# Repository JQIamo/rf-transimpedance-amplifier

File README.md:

# RF Transimpedance Amplifier

An AC-coupled transimpedance amplifier, for use in (eg) beatnote or PDH locks.

Still a work in progress, more info to come soon.

NOTE: Despite git commit history, the pdh-photodiode branch is more up to date than master for the ac-coupled transimpedance amp (I believe...)

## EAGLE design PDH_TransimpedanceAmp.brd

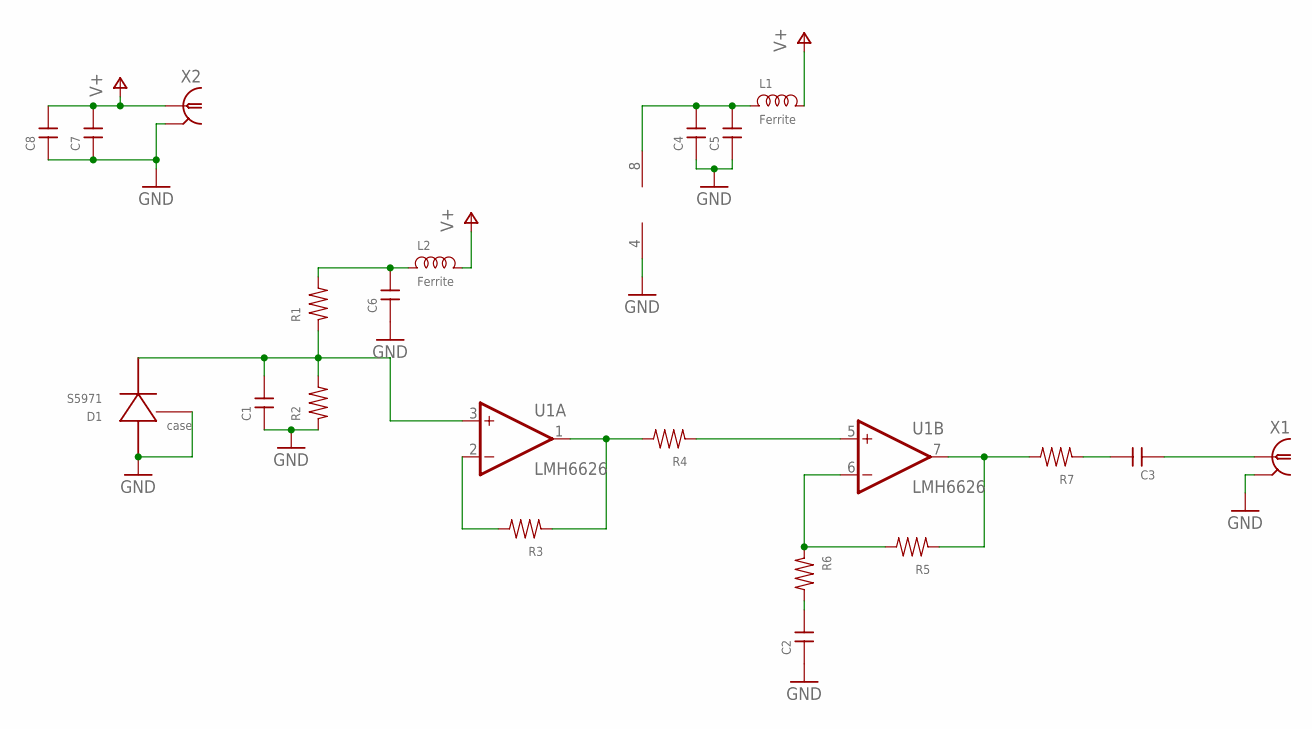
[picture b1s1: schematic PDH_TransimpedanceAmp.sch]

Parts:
C1, C2, C3, C4, C8: CAP0402; 0402
C5, C6, C7: CAP0805; 0805
D1: S5971; S5971-CASE
L1, L2: Ferrite; 0805
R1, R2, R3, R4, R5, R6, R7: RES0402; 0402
U1: LMH6626; SO08
X1, X2: UMC

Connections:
GND: C1.1, C2.1, C4.1, C5.1, C6.1, C7.1, C8.1, D1.P$2 (CASE), D1.P$3 (ANODE), R2.1, U1.4 (V-), X1.P$2 (2), X1.P$3 (2), X2.P$2 (2), X2.P$3 (2)
unnamed: C1.2, D1.P$1 (CATHODE), R1.1, R2.2, U1.3 (+IN)
unnamed: R5.2, R6.1, U1.6 (-IN)
unnamed: C3.2, R7.1
unnamed: R3.2, U1.2 (-IN)
unnamed: R3.1, R4.2, U1.1 (OUT)
unnamed: R4.1, U1.5 (+IN)
unnamed: C2.2, R6.2
unnamed: R5.1, R7.2, U1.7 (OUT)
unnamed: C6.2, L2.1, R1.2
unnamed: C4.2, C5.2, L1.1, U1.8 (V+)
unnamed: C3.1, X1.P$1 (1)
V+: C7.2, C8.2, L1.2, L2.2, X2.P$1 (1)

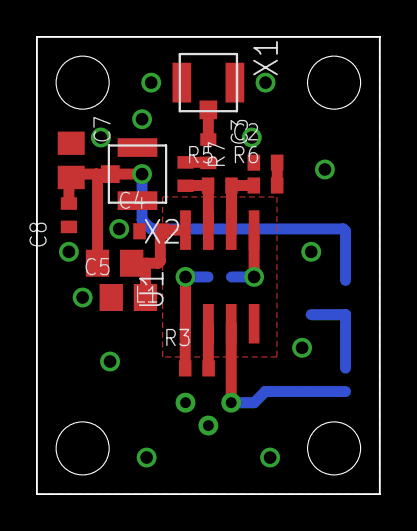
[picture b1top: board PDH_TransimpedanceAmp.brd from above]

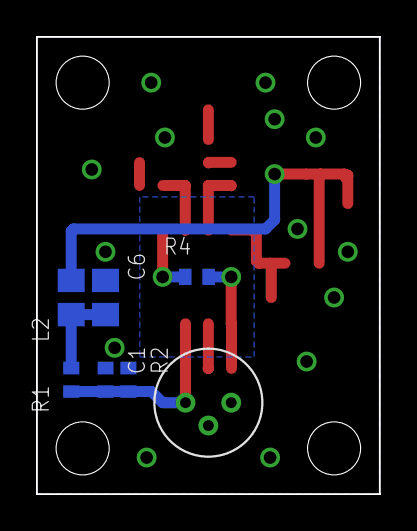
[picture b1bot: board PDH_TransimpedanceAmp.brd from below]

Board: 2 copper layers, 19.1 x 25.4 mm, 21 parts (7 on the bottom side), 13 nets.

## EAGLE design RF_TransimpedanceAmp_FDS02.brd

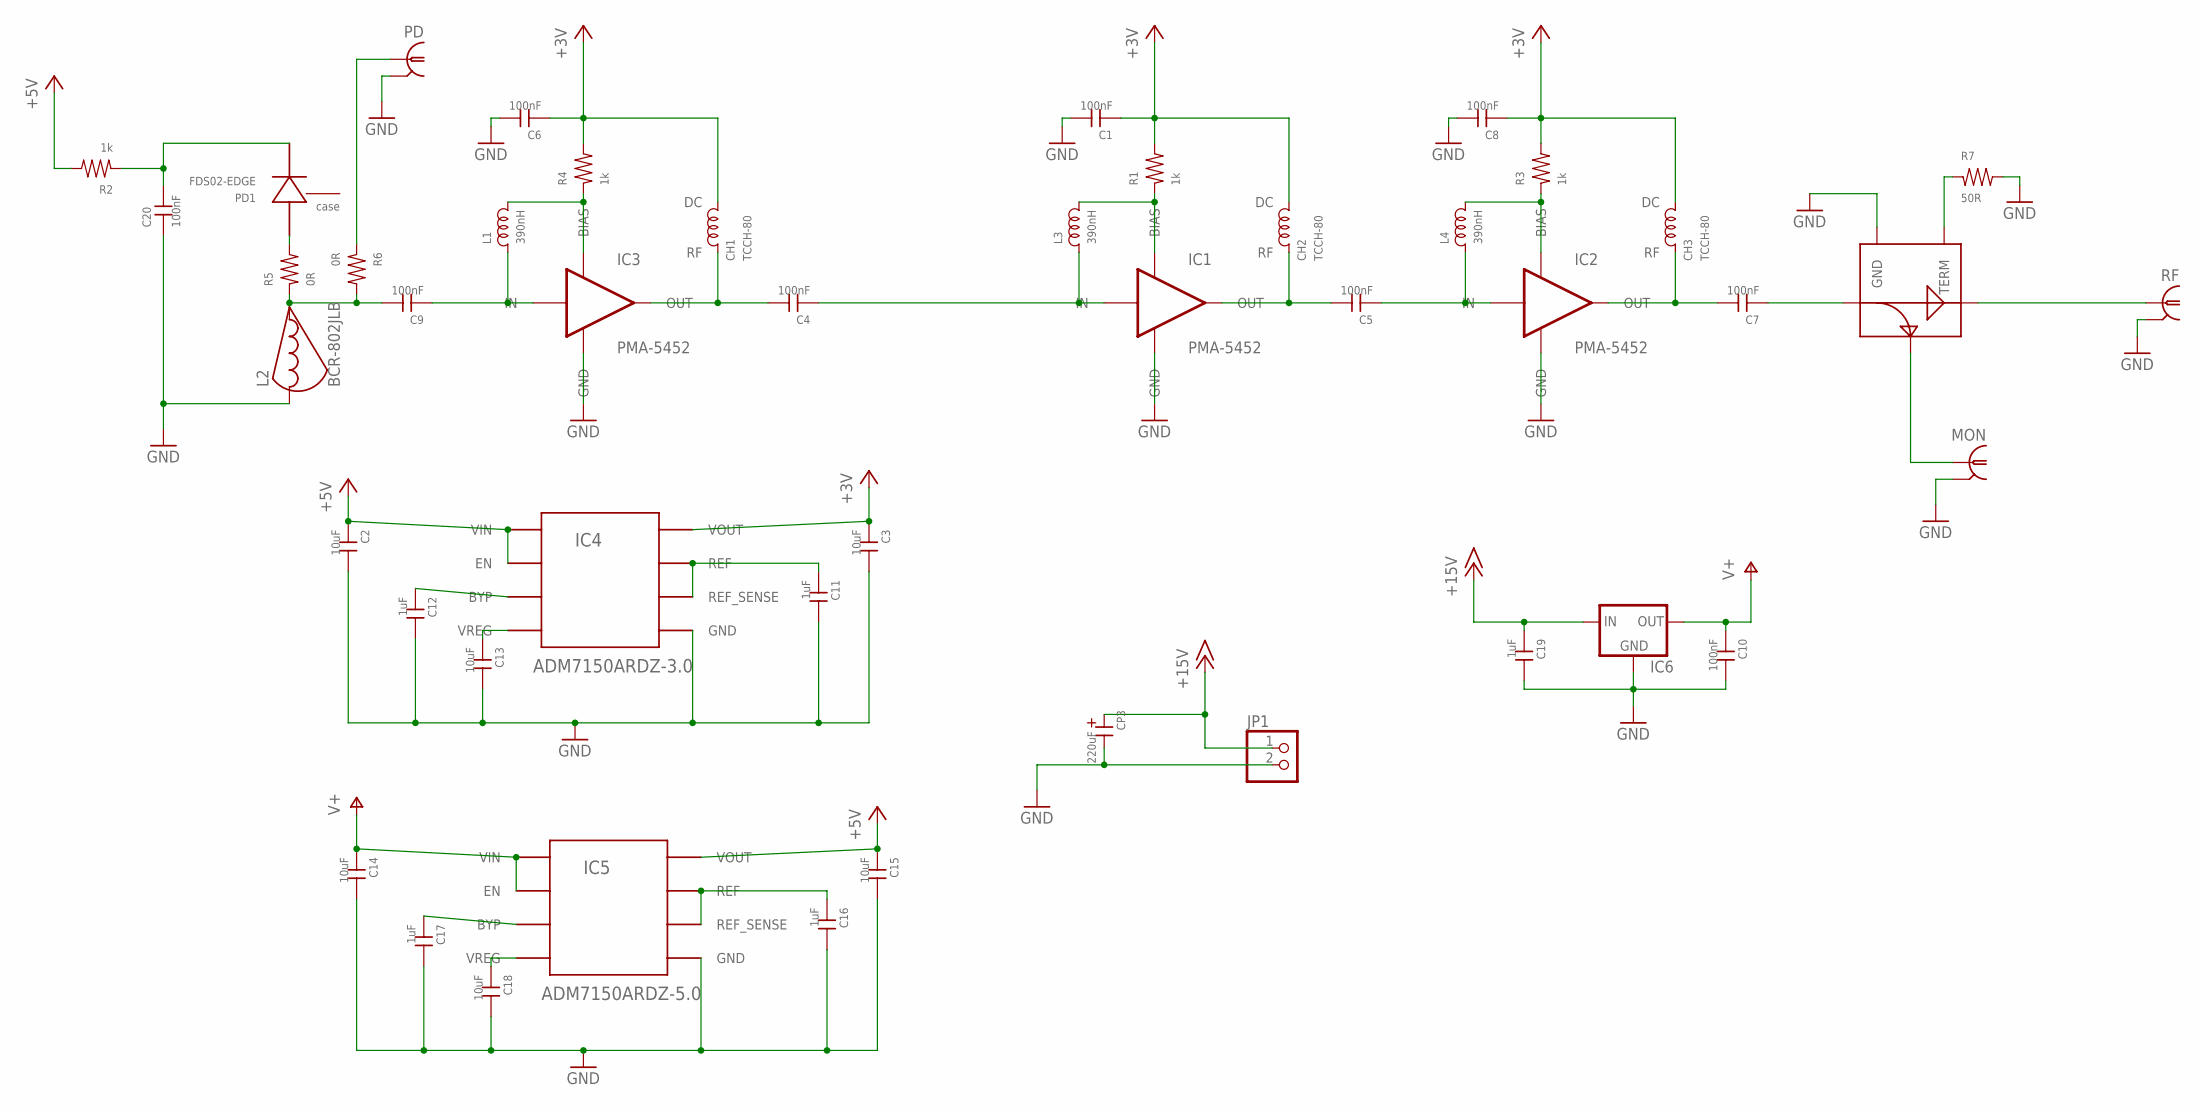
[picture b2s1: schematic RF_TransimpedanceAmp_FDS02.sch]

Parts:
C1, C4, C5, C6, C7, C8, C9, C20: 100nF; 0402
C2, C3, C13, C14, C15, C18: 10uF; 1210
C10: 100nF; 0603
C11, C12, C16, C17, C19: 1uF; 0603
CH1, CH2, CH3: TCCH-80; GU1604
CP3: 220uF; PANASONIC_F
IC1, IC2, IC3: PMA-5452; DQ849
IC4: ADM7150ARDZ-3.0; SO08
IC5: ADM7150ARDZ-5.0; SO08
IC6: 78XX-TO220; TO220
JP1: PINHD-1X2; 1X02
L1, L3, L4: 390nH; 0402
L2: BCR-802JLB; BCR-MED
MON: SMAJ502-bulkhead; SMA-EDGE; PARTNO CONSMA006.062-ND
PD: SMAJ502-bulkhead; SMA-EDGE; PARTNO CONSMA006.062-ND
PD1: FDS02-EDGE; FDS02-SIDEMOUNT
R1, R2, R3, R4: 1k; 0402
R5, R6: 0R; 0402
R7: 50R; 0603
RF: SMAJ502; SMA-EDGE
U$1: ADC-10-4; BH292

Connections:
+3V: C1.1, C3.1, C6.1, C8.1, CH1.P$3 (DC), CH2.P$3 (DC), CH3.P$3 (DC), IC4.2 (VOUT), R1.2, R3.2, R4.2
+5V: C2.1, C15.1, IC4.7 (EN), IC4.8 (VIN), IC5.2 (VOUT), R2.2
+15V: C19.1, CP3.+, IC6.1 (IN), JP1.1
GND: C1.2, C2.2, C3.2, C6.2, C8.2, C10.2, C11.2, C12.2, C13.2, C14.2, C15.2, C16.2, C17.2, C18.2, C19.2, C20.1, CP3.-, IC1.P$GND (GND), IC2.P$GND (GND), IC3.P$GND (GND), IC4.4 (GND), IC5.4 (GND), IC6.2 (GND), JP1.2, L2.2, MON.G@1 (2), MON.G@2 (2), MON.G@3 (2), MON.G@4 (2), PD.G@1 (2), PD.G@2 (2), PD.G@3 (2), PD.G@4 (2), R7.2, RF.G@1 (2), RF.G@2 (2), RF.G@3 (2), RF.G@4 (2), U$1.P2 (GND)
unnamed: C11.1, IC4.5 (REF_SENSE), IC4.6 (REF)
unnamed: C5.2, CH2.P$1 (RF), IC1.P$6 (OUT)
unnamed: IC1.P$7 (BIAS), L3.2, R1.1
unnamed: RF.1, U$1.P6 (OUT)
unnamed: C20.2, PD1.P$1 (CATHODE), R2.1
unnamed: C4.2, CH1.P$1 (RF), IC3.P$6 (OUT)
unnamed: C9.2, L2.1, R5.1, R6.2
unnamed: C7.2, CH3.P$1 (RF), IC2.P$6 (OUT)
unnamed: IC3.P$7 (BIAS), L1.2, R4.1
unnamed: IC2.P$7 (BIAS), L4.2, R3.1
unnamed: C7.1, U$1.P1 (IN)
unnamed: MON.1, U$1.P3 (COUP)
unnamed: C12.1, IC4.3 (BYP)
unnamed: C13.1, IC4.1 (VREG)
unnamed: C16.1, IC5.5 (REF_SENSE), IC5.6 (REF)
unnamed: PD1.P$3 (ANODE), R5.2
unnamed: PD.1, R6.1
unnamed: C17.1, IC5.3 (BYP)
unnamed: C18.1, IC5.1 (VREG)
unnamed: R7.1, U$1.P4 (TERM)
RFPD: C9.1, IC3.P$1 (IN), L1.1
RFPD1: C4.1, IC1.P$1 (IN), L3.1
RFPD2: C5.1, IC2.P$1 (IN), L4.1
V+: C10.1, C14.1, IC5.7 (EN), IC5.8 (VIN), IC6.3 (OUT)

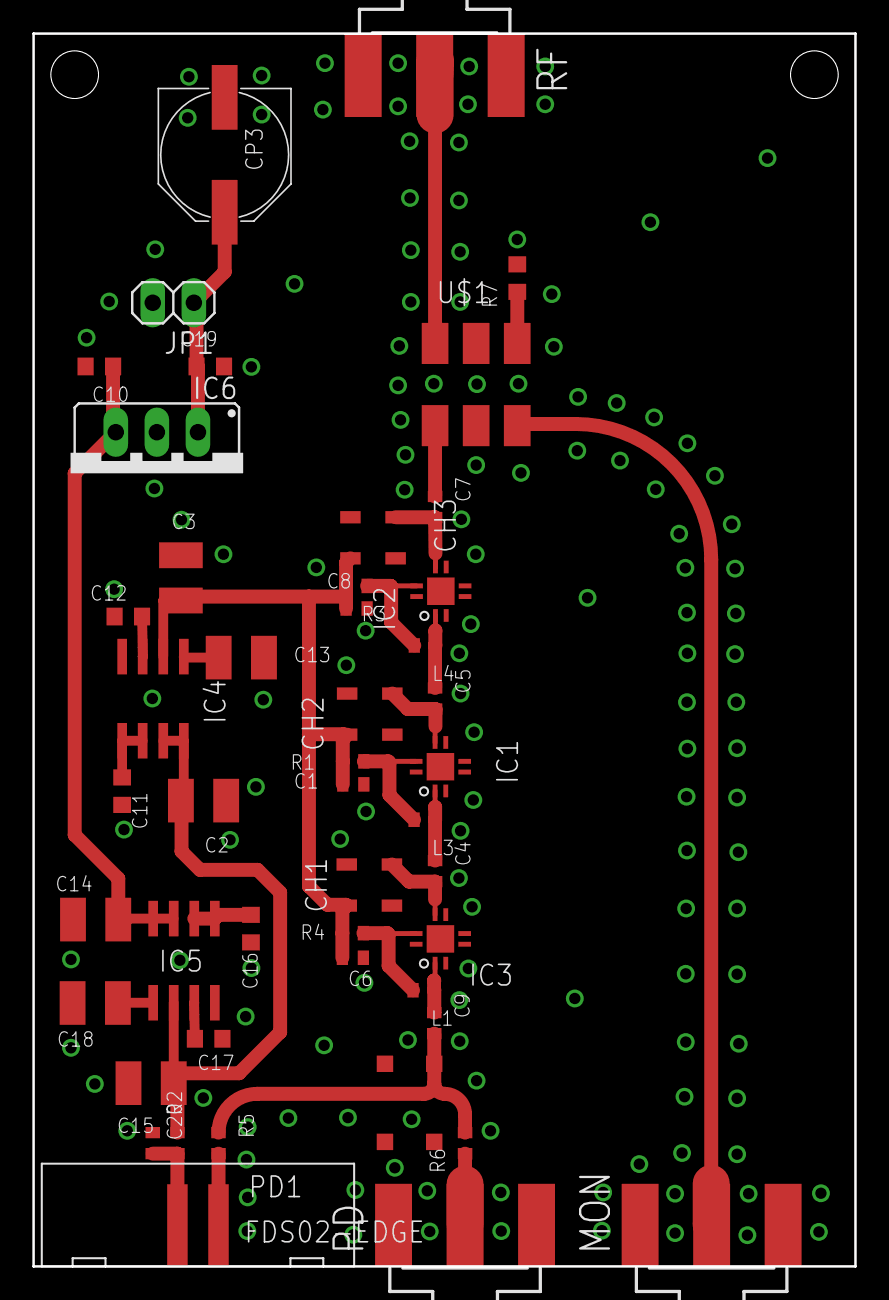
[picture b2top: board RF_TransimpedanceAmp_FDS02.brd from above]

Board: 2 copper layers, 50.8 x 76.2 mm, 47 parts (0 on the bottom side), 28 nets.

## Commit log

2014-11-01 Initial schematic and a bit of layout for an RF transimpedance amplifier.
2014-11-01 Updated description of how schematic works/plugs together.
2014-11-03 Schematic done; routing in progress. Want to check with alessandro.
2014-11-21 Initial commit for separate schematic, for Thorlabs FDS02 fiber-connected photodiode
2014-11-25 First draft schematic and layout for FDS02 transimpedance amplifier.
    * Low transimpedance gain, followed by low-noise RF amplifier.
    * FDS02 is FC-connectorized, mount on bottom of board and standoff from front panel.
    TODO:
    * Remove -5V supply?
    * Compare OPA847 vs some FET-input op amp
    * Filtering on PD bias voltage?
2014-11-25 Minor tweaks to schematic notes; need to check 50 ohm trace width then ready to print.
2014-11-25 Adjusted center pad via in RF amp
2014-11-25 Removed OPA847, using low-noise amplifiers with 50 ohm input as transimpedance gain.
2014-11-25 Adjusted grounding vias, created gerbers
2014-11-26 V0.9 of RF_Transimpedance Amp for FDS02 diode
2014-11-26 Added pdf prints of soldermask, for use with Dynamask 5000 process.
2015-01-01 Added .gitignore and README files
2015-01-19 Added third stage amplifier, fixed layout issues.
2015-01-20 Moved mounting hole to rectangular grid
2015-02-01 Added local library to the project.
    I think we should try to make this standard practice -- import components
    to local project repository.
2015-02-01 Added schematic and board for PDH transimpedance amp.
    For lower RF frequencies; RF amp version only goes to
    50 MHz. This uses an op amp with GBP of 1.5GHz though.
2015-02-05 Fixed PD net connection; added BW limiting capacitor
2015-03-13 Misc store point; pushing for work at home
2015-03-20 Ripped up traces in preparation for adding additional SMA and switch for beatnote
2015-03-22 Added SMA photodiode input; output monitor
    Switch between FDS02 or other photodiode by soldering 0ohm jumper.
2015-03-30 minor tweaks to board layout
2015-08-03 schematic and layout done; a little packed so going to reduce filtering caps
2015-08-06 Printed; prototyped and seems to be working
2016-01-30 Added library temp file to gitignore
2016-01-30 Added AC-coupled transimpedance amp for PDH
2016-01-30 updated readme with comment about branches in reorganization
